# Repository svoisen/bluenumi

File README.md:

Bluenumi Clock
==============

Bluenumi is a custom-designed 4-digit numitron clock featuring:

* Retro glowing numitron display featuring Russian IV-9 numitron tubes
* A DS1307 real time clock with backup battery for accurate timekeeping and alarm memory preservation during loss of power
* Blue LED underlighting for each digit, with pre-programmed fade patterns
* Laser cut acrylic case
* Programmable alarm
* 12- or 24-hour operating mode with AM/PM indicator light
* Easy display blanking for nighttime use and tube life preservation
* 100% open source hardware and software
* Arduino programming compatibility using standard TTL serial

For more information, or to order a clock kit or fully assembled, visit: [http://www.etsy.com/shop/VoisenDesign](http://www.etsy.com/shop/VoisenDesign).

Parts list (BOM), assembly instructions, and user's guide are [available on the wiki](https://github.com/svoisen/bluenumi/wiki).

Images
------

Firmware License
----------------

Copyright (C) 2009 - 2011 [Sean Voisen](http://sean.voisen.org)

Firmware code is released under the GNU GPL version 3:

This program is free software: you can redistribute it and/or modify it under the terms of the GNU General Public License as published by the Free Software Foundation, either version 3 of the License, or (at your option) any later version.

This program is distributed in the hope that it will be useful, but WITHOUT ANY WARRANTY; without even the implied warranty of MERCHANTABILITY or FITNESS FOR A PARTICULAR PURPOSE.  See the GNU General Public License for more details.

You should have received a copy of the GNU General Public License along with this program.  If not, see <http://www.gnu.org/licenses/>.

Schematics and Board Layout License
-----------------------------------

Copyright (C) 2009 - 2011 [Sean Voisen](http://sean.voisen.org)

Schematics and board layout are released under the [Creative Commons Attribution-ShareAlike 3.0 Unported](http://creativecommons.org/licenses/by-sa/3.0/) license.

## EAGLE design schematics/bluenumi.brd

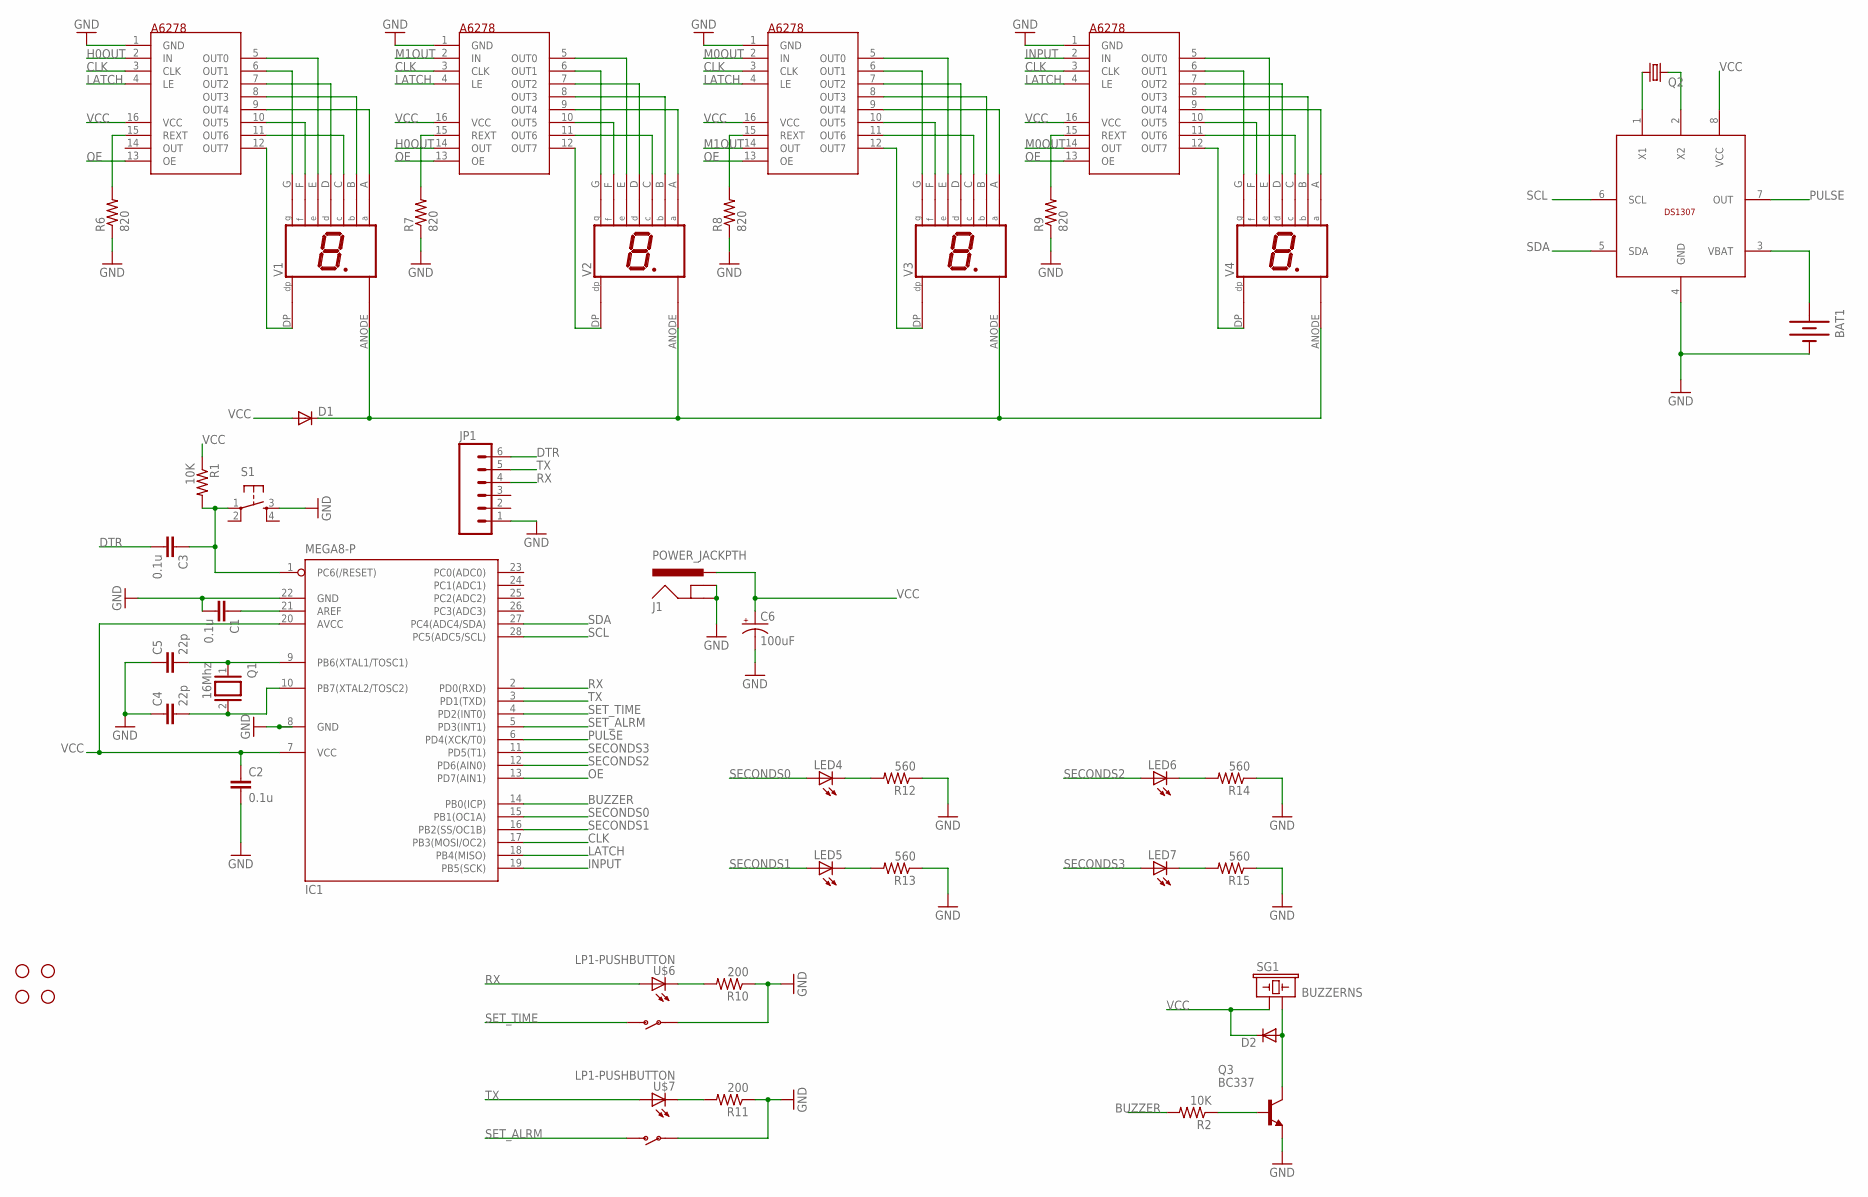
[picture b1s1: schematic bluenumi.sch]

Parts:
BAT1: BATTERY20PTH; BATTCOM_20MM_PTH
C1, C2, C3: 0.1u; CAP-PTH-SMALL
C4, C5: 22p; CAP-PTH-SMALL
C6: 100uF; CPOL-RADIAL-10UF-25V
D1, D2: DIODEPTH; DIODE-1N4001
IC1: MEGA8-P; DIL28-3
J1: POWER_JACKPTH; POWER_JACK_PTH
JP1: M06LOCK; 1X06_LOCK
LED4, LED5, LED6, LED7: LED5MM
Q1: 16Mhz; QS
Q2: CRYSTALTC26H; TC26H
Q3: BC337; TO92
R1, R2: 10K; AXIAL-0.3
R6, R7, R8, R9: 820; AXIAL-0.3
R10, R11: 200; AXIAL-0.3
R12, R13, R14, R15: 560; AXIAL-0.3
S1: TAC_SWITCHPTH; TACTILE-PTH
SG1: BUZZERNS; BUZZER-12MM-NS
U$1: TLC5916; DIL16
U$2, U$3, U$4: A6278EAT; DIL16
U$5: DS1307; DIL08
U$6, U$7: LP1-PUSHBUTTON
U$8, U$9, U$10, U$11: STAND-OFF
V1, V2, V3, V4: IV-9-UNDERLIT; 9PINTUBE-WIDE

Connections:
BUZZER: IC1.14 (PB0(ICP)), R2.P$2 (2)
CLK: IC1.17 (PB3(MOSI/OC2)), U$1.3 (CLK), U$2.3 (CLK), U$3.3 (CLK), U$4.3 (CLK)
DTR: C3.2, JP1.6
GND: BAT1.2 (-), C1.2, C2.2, C4.1, C5.1, C6.2 (-), IC1.8 (GND), IC1.22 (GND), J1.GND, J1.GNDBREAK, JP1.1, Q3.1 (E), R6.P$1 (1), R7.P$1 (1), R8.P$1 (1), R9.P$1 (1), R10.P$1 (1), R11.P$1 (1), R12.P$1 (1), R13.P$1 (1), R14.P$1 (1), R15.P$1 (1), S1.3, U$1.1 (GND), U$2.1 (GND), U$3.1 (GND), U$4.1 (GND), U$5.4 (GND), U$6.S2, U$7.S2
H0OUT: U$1.2 (IN), U$2.14 (OUT)
INPUT: IC1.19 (PB5(SCK)), U$4.2 (IN)
LATCH: IC1.18 (PB4(MISO)), U$1.4 (LE), U$2.4 (LE), U$3.4 (LE), U$4.4 (LE)
M0OUT: U$3.2 (IN), U$4.14 (OUT)
M1OUT: U$2.2 (IN), U$3.14 (OUT)
unnamed: U$1.5 (OUT0), V1.E
unnamed: U$1.6 (OUT1), V1.G
unnamed: U$1.7 (OUT2), V1.D
unnamed: U$1.8 (OUT3), V1.B
unnamed: U$1.9 (OUT4), V1.A
unnamed: U$1.10 (OUT5), V1.F
unnamed: U$1.11 (OUT6), V1.C
unnamed: U$1.12 (OUT7), V1.DP
unnamed: R11.P$2 (2), U$7.CATHODE
unnamed: U$2.12 (OUT7), V2.DP
unnamed: C5.2, IC1.9 (PB6(XTAL1/TOSC1)), Q1.1
unnamed: U$2.6 (OUT1), V2.G
unnamed: U$2.5 (OUT0), V2.E
unnamed: U$2.7 (OUT2), V2.D
unnamed: U$2.8 (OUT3), V2.B
unnamed: U$2.9 (OUT4), V2.A
unnamed: U$2.10 (OUT5), V2.F
unnamed: U$2.11 (OUT6), V2.C
unnamed: D1.C, V1.ANODE, V2.ANODE, V3.ANODE, V4.ANODE
unnamed: Q2.1, U$5.1 (X1)
unnamed: Q2.2, U$5.2 (X2)
unnamed: C4.2, IC1.10 (PB7(XTAL2/TOSC2)), Q1.2
unnamed: C3.1, IC1.1 (PC6(/RESET)), R1.P$2 (2), S1.1
unnamed: C1.1, IC1.21 (AREF)
unnamed: U$3.12 (OUT7), V3.DP
unnamed: U$3.11 (OUT6), V3.C
unnamed: U$3.10 (OUT5), V3.F
unnamed: U$3.9 (OUT4), V3.A
unnamed: U$3.8 (OUT3), V3.B
unnamed: U$3.7 (OUT2), V3.D
unnamed: U$3.6 (OUT1), V3.G
unnamed: U$3.5 (OUT0), V3.E
unnamed: R6.P$2 (2), U$1.15 (REXT)
unnamed: Q3.2 (B), R2.P$1 (1)
unnamed: D2.A, Q3.3 (C), SG1.- (2)
unnamed: R7.P$2 (2), U$2.15 (REXT)
unnamed: R8.P$2 (2), U$3.15 (REXT)
unnamed: R9.P$2 (2), U$4.15 (REXT)
unnamed: R10.P$2 (2), U$6.CATHODE
unnamed: U$4.11 (OUT6), V4.C
unnamed: U$4.10 (OUT5), V4.F
unnamed: U$4.9 (OUT4), V4.A
unnamed: U$4.8 (OUT3), V4.B
unnamed: U$4.7 (OUT2), V4.D
unnamed: U$4.6 (OUT1), V4.G
unnamed: U$4.5 (OUT0), V4.E
unnamed: LED4.K (C), R12.P$2 (2)
unnamed: U$4.12 (OUT7), V4.DP
unnamed: LED5.K (C), R13.P$2 (2)
unnamed: LED6.K (C), R14.P$2 (2)
unnamed: LED7.K (C), R15.P$2 (2)
unnamed: BAT1.1 (+), U$5.3 (VBAT)
OE: IC1.13 (PD7(AIN1)), U$1.13 (OE), U$2.13 (OE), U$3.13 (OE), U$4.13 (OE)
PULSE: IC1.6 (PD4(XCK/T0)), U$5.7 (OUT)
RX: IC1.2 (PD0(RXD)), JP1.4, U$6.ANODE
SCL: IC1.28 (PC5(ADC5/SCL)), U$5.6 (SCL)
SDA: IC1.27 (PC4(ADC4/SDA)), U$5.5 (SDA)
SECONDS0: IC1.15 (PB1(OC1A)), LED4.A
SECONDS1: IC1.16 (PB2(SS/OC1B)), LED5.A
SECONDS2: IC1.12 (PD6(AIN0)), LED6.A
SECONDS3: IC1.11 (PD5(T1)), LED7.A
SET_ALRM: IC1.5 (PD3(INT1)), U$7.S1
SET_TIME: IC1.4 (PD2(INT0)), U$6.S1
TX: IC1.3 (PD1(TXD)), JP1.5, U$7.ANODE
VCC: C2.1, C6.1 (+), D1.A, D2.C, IC1.7 (VCC), IC1.20 (AVCC), J1.PWR, R1.P$1 (1), SG1.+ (1), U$1.16 (VCC), U$2.16 (VCC), U$3.16 (VCC), U$4.16 (VCC), U$5.8 (VCC)

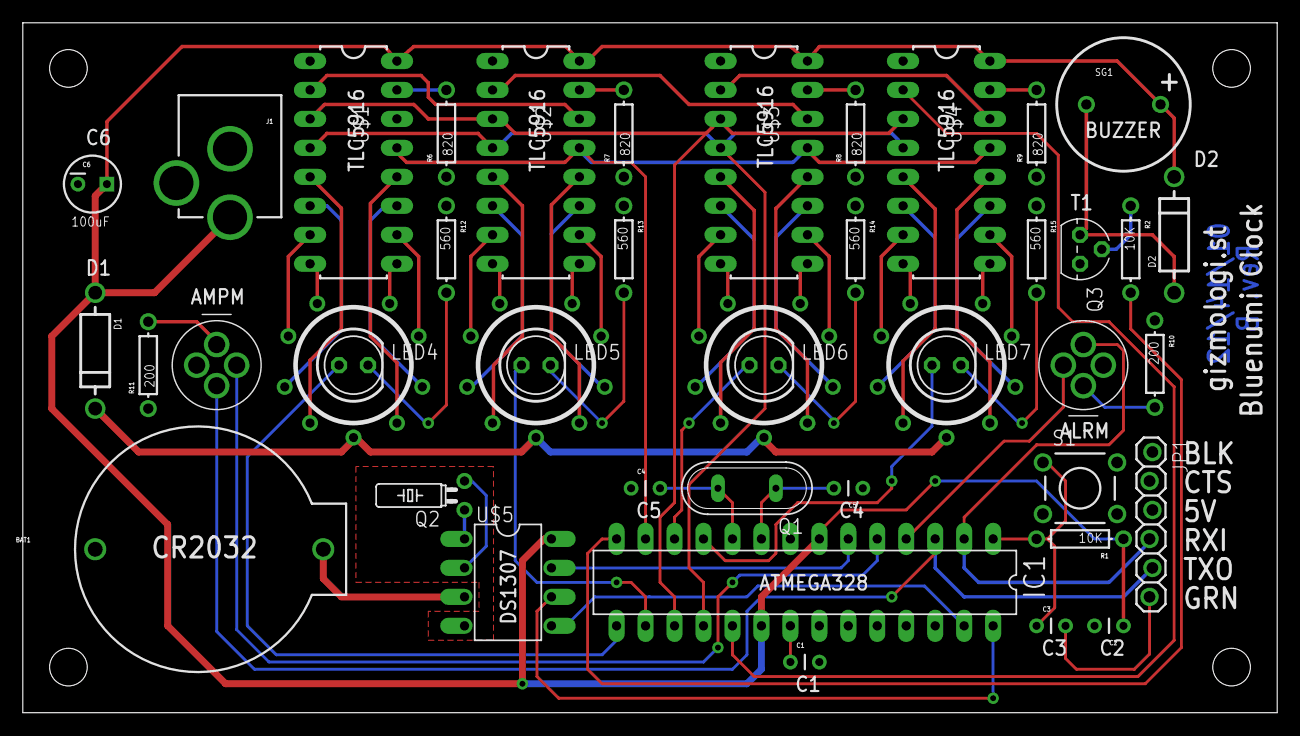
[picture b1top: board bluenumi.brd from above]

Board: 2 copper layers, 110.0 x 60.5 mm, 48 parts (0 on the bottom side), 74 nets.

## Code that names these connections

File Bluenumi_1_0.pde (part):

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/*******************************************************************************
 * Pin Mappings
 /*****************************************************************************/
#define SECONDS0_PIN 9 // LED under 10s hour
#define SECONDS1_PIN 10 // LED under 1s hour
#define SECONDS2_PIN 11 // LED under 10s minute
#define SECONDS3_PIN 3 // LED under 1s minute
#define DATA_PIN 13 // Data input to A6278 shift registers
#define LATCH_PIN 12 // Latch control for A6278 shift registers
#define CLK_PIN 6 // Clock for A6278 shift registers
#define OE_PIN 7 // Output enable on A6278 shift registers, active low
#define AMPM_PIN 0 // Both RX and used for AMPM indicator LED
#define ALRM_PIN 1 // Both TX and used for alarm indicator LED
#define PIEZO_PIN 8 // Piezo alarm
#define HZ_PIN 4 // 1 Hz pulse from DS1307 RTC
#define LEFT_BTN_PIN 2 // Time set/left button
#define RIGHT_BTN_PIN 5 // Alarm set/right button

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void setup()
{
  // Set up pin modes
  pinMode( SECONDS0_PIN, OUTPUT );
  pinMode( SECONDS1_PIN, OUTPUT );
  pinMode( SECONDS2_PIN, OUTPUT );
  pinMode( SECONDS3_PIN, OUTPUT );
  pinMode( DATA_PIN, OUTPUT );
  pinMode( LATCH_PIN, OUTPUT );
  pinMode( CLK_PIN, OUTPUT );
  pinMode( OE_PIN, OUTPUT );
  pinMode( AMPM_PIN, OUTPUT );
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  bool twelveHourMode, ampm;
  DS1307RTC.getDateTime( &second, &minute, &hour, &dayOfWeek, &dayOfMonth, &month, &year, &twelveHourMode, &ampm );
  
  digitalWrite( LATCH_PIN, LOW );
  shiftOut( DATA_PIN, CLK_PIN, MSBFIRST, numbers[hour/10] );
  shiftOut( DATA_PIN, CLK_PIN, MSBFIRST, numbers[hour%10] );
  shiftOut( DATA_PIN, CLK_PIN, MSBFIRST, numbers[minute/10] );
  shiftOut( DATA_PIN, CLK_PIN, MSBFIRST, numbers[minute%10] );
  digitalWrite( LATCH_PIN, HIGH );
  
  digitalWrite( AMPM_PIN, (ampm ? HIGH : LOW) ); // Also output AMPM indicator light
}
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void blankDisplay()
{
  digitalWrite( OE_PIN, HIGH );
  digitalWrite( SECONDS0_PIN, LOW );
  digitalWrite( SECONDS1_PIN, LOW );
  digitalWrite( SECONDS2_PIN, LOW );
  digitalWrite( SECONDS3_PIN, LOW );
  digitalWrite( AMPM_PIN, LOW );
  digitalWrite( ALRM_PIN, LOW );
}
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
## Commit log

2010-02-13 Move code to firmware folder
2010-02-13 Add Eagle files
2011-10-30 Use built-in Arduino I2C library Temp disable interrupts for buttons
2011-10-30 Rename folders Add README
2011-10-31 Update to new coding conventions
2011-10-31 Update copyright
2011-11-02 Fix interrupt issues Begin display blinking for time set mode
2011-11-02 Use function pointers for mode map instead of giant switch statement
2011-11-03 Use enumerations for modes
2011-11-05 Continue improving state maching handling
2011-11-06 Add more mode handlers, continue work on time set
2011-11-07 Clean up comments Begin breaking up display code to separate class
2011-11-07 Cleanup Display cpp/h Cleanup DS1307 Continue work on set time mode handlers
2011-11-08 Fix bug with setting minute ones
2011-11-08 Begin adding cycle handlers
2011-11-08 Finish time setting mechanism Improve long button presses
2011-11-09 Use Bounce library Show Hr when choosing 12/24 hour
2011-11-10 Improve time setting Add setting AM/PM
2011-11-10 Begin work on LED pattern generation
2011-11-10 Add breathing pattern
2011-11-11 Rename Pattern to LEDController Adding rolling breathe pattern
2011-11-11 Begin work on AudioController and pre-programmed melodies
2011-11-28 Adding support for run blank mode
2011-11-28 Update README with new license for schematics
2011-11-29 Update README Add beeps Tune debounce and beep intervals
2011-11-29 Begin work on alarm setting
2011-11-29 Add melody when moving to set time mode
2011-12-09 Add alarm functionality Update to get things to compile with Arudino 1.0
2011-12-09 Temp set beep to 2048 Fix problem with initial alarm hours setting
2011-12-11 Change font to use "curly" 6 and 9 Include display mapping in comments Pause blinking temporarily when cycling through values for improved usability
2011-12-11 Add functions for reading/writing DS1307 general purpose RAM
2011-12-12 Save alarm to RAM Fetch alarm from RAM on restart from mains power Fix bug with buffer overflow in number of run modes
2011-12-12 Fix bugs with alarm retention on powerup
2011-12-12 Add ability to turn off alarm
2011-12-12 Fix bug with alarm not turning on in run blank mode
2011-12-14 Clean up licenses to make consistently GPL v3 Clean up indenting on Bounce
2011-12-14 Fix skipNextBlink bug when flashing is off Add melody when switching to set time mode
2011-12-14 Minor melody tweaks
2011-12-14 Flash alarm time when enabling alarm
2011-12-14 Add LICENSE
2011-12-15 Use uppercase M in AM/PM
2011-12-15 Fix bug where switch from 24- to 12-hour mode could leave hours at 00
2011-12-23 Add gitignore Update schematic to include reverse EMF protection diode Drive buzzer via transistor Remove 1K resistors on TX/RX Remove extra power diode and jumpers
2011-12-23 Clean up board layout
2012-01-06 Fix bug where large values of millis() cause stuttering in LED fade pattern
2012-01-15 Create gerber files Update board and schematic so that LED PWM is not on Arduino pins 3 or 11
2012-01-15 Remove unused gerber files
2012-08-12 Update pin mappings to match board revision B layout
2012-09-08 Update gitignore Fix mis-mapped buttons
2012-09-12 Retab Bounce.cpp Fix debounce interval and interrupt used for time set pin
2012-10-06 Fix README
2012-10-07 Change debounce interval to 20
2012-10-13 Add Castlevania melody

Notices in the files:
Bluenumi_1_0.pde:
Copyright (C) 2010 Gizmologist, LLC. All rights reserved.
